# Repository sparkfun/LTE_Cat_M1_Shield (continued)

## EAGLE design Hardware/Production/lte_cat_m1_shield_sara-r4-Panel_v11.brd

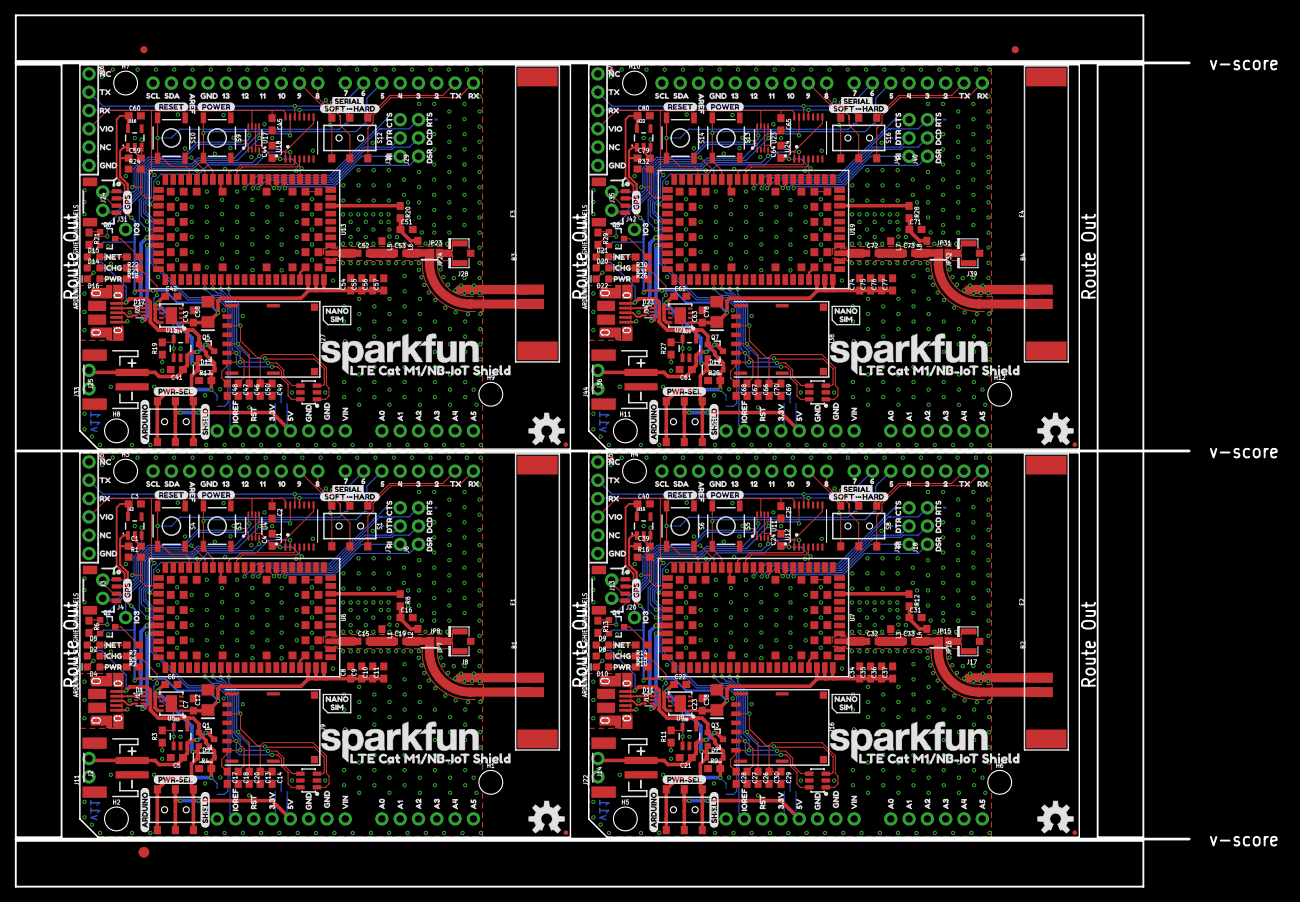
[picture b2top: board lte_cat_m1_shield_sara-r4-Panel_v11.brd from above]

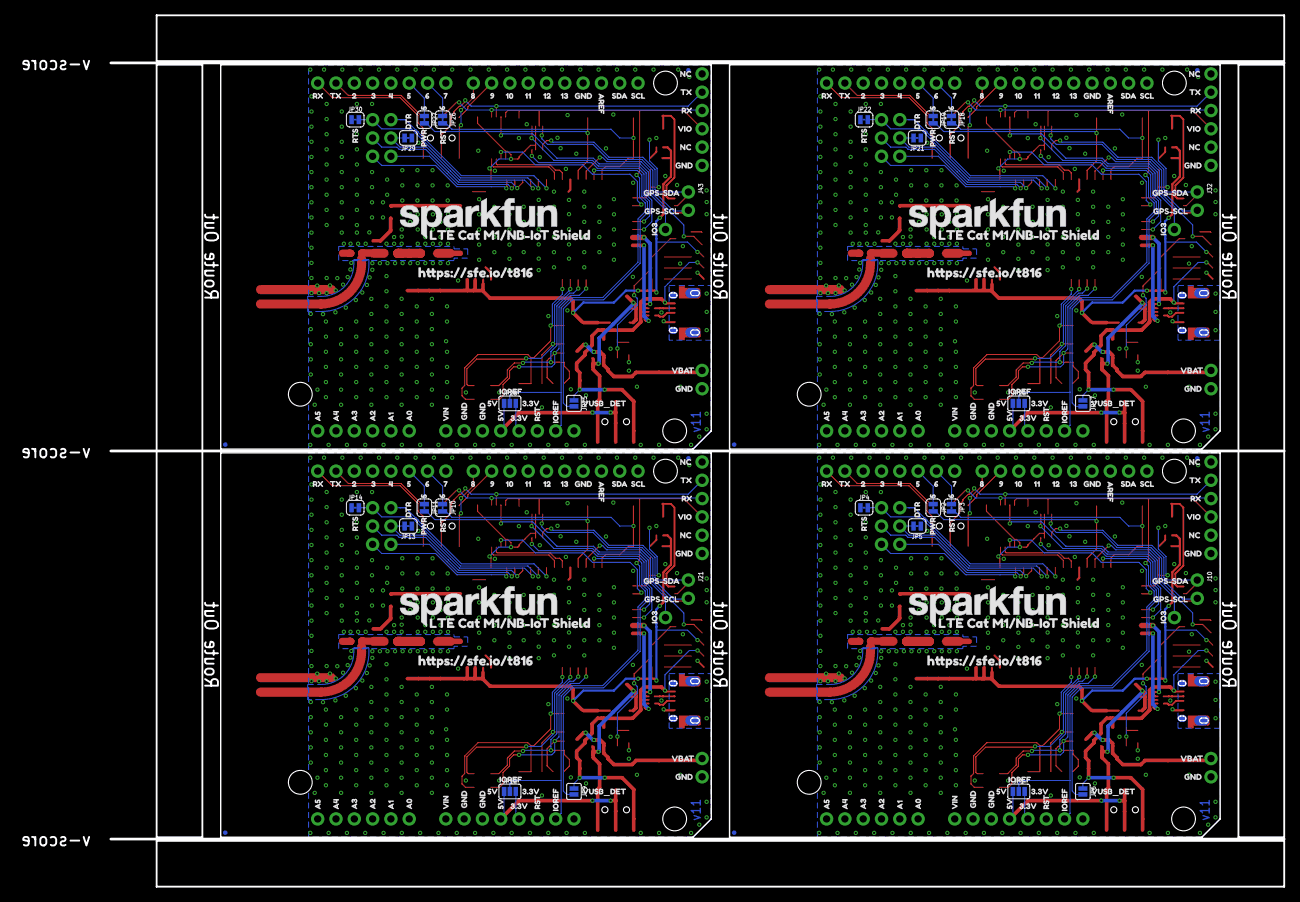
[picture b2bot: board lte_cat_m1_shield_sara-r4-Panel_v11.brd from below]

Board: 2 copper layers, 162.8 x 120.9 mm, 767 parts (256 on the bottom side), 240 nets.

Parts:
B1, B2, B3, B4: ARDUINO_UNO_R3_SHIELDNOLABELS; UNO_R3_SHIELD_NOLABELS
C1, C3, C39, C40, C59, C60, C79, C80: 1.0uF; 0603
C2, C4, C8, C13, C24, C25, C30, C34, C44, C45, C50, C54, C64, C65, C70, C74: 0.1uF; 0603
C5, C6, C7, C21, C22, C23, C41, C42, C43, C61, C62, C63: 4.7uF; 0603
C9, C35, C55, C75: 10nF; 0603
C10, C15, C32, C36, C52, C56, C72, C76: 15pF; 0603
C11, C37, C57, C77: 68pF; 0603
C12, C38, C58, C78: 100uF; 1206-POLAR
C14, C17, C18, C20, C26, C27, C28, C29, C46, C47, C48, C49, C66, C67, C68, C69: 47pF; 0603
C16, C31, C51, C71: DNP; 0603
C19, C33, C53, C73: 0; 0603
D1, D11, D17, D23: PRTR5V0U2F; SOT886
D2, D8, D14, D20: Yellow; LED-0603
D3, D7, D13, D19: 1A/23V/620mV; SOD-323
D4, D10, D16, D22: RED; LED-0603
D5, D9, D15, D21: BLUE; LED-0603
D6, D12, D18, D24: DT1042-04SO-7; SOT23-6L
E1, E2, E3, E4: MOLEX-146200; MOLEX_146200
E$1, E$2: FIDUCIAL-1X2
E$3: FIDUCIAL-1.5X3
FD1, FD2, FD3, FD4, FD5, FD6, FD7, FD8, FD9, FD10, FD11, FD12, FD13, FD14, FD15, FD16: FIDUCIALUFIDUCIAL; FIDUCIAL-MICRO
H1, H2, H3, H4, H5, H6, H7, H8, H9, H10, H11, H12: STAND-OFF
J1, J12, J23, J34: USB-MICROB-PTH-MILL
J2, J14, J25, J36: JST-2-SMD
J3, J13, J24, J35: 1X04_1MM_RA
J4, J20, J31, J42: 1X01_NO_SILK
J5, J15, J26, J37: 1X06_NO_SILK
J6, J7, J18, J19, J29, J30, J40, J41: 1X03_NO_SILK
J8, J17, J28, J39: U.FL
J9, J16, J27, J38: NANO_SIM; NANO_SIM_WURTH_693043020611
J10, J11, J21, J22, J32, J33, J43, J44: 1X02_NO_SILK
JP1, JP12, JP20, JP28: IOREF-SEL; SMT-JUMPER_3_NO_SILK
JP2, JP3, JP10, JP11, JP18, JP19, JP26, JP27: JUMPER-SMT_2_NC_TRACE_SILK; SMT-JUMPER_2_NC_TRACE_SILK
JP4, JP5, JP13, JP14, JP21, JP22, JP29, JP30: SMT-JUMPER_2_NC_TRACE_SILK
JP6, JP9, JP17, JP25: VUSB_DET; SMT-JUMPER_2_NO_SILK
JP7, JP16, JP24, JP32: J-CHIP; SMT-JUMPER_2_NC_TRACE_NO-SILK
JP8, JP15, JP23, JP31: J-U.FL; SMT-JUMPER_2_NO_NO-SILK
L1, L3, L5, L7: 39nH; 0603
L2, L4, L6, L8: DNP; 0603
LOGO1, LOGO3, LOGO5, LOGO6, LOGO8, LOGO9, LOGO11, LOGO12: SFE_LOGO_NAME.2_INCH; SFE_LOGO_NAME_.2
LOGO2, LOGO4, LOGO7, LOGO10: OSHW-LOGOM; OSHW-LOGO-M
Q1, Q3, Q5, Q7: 2.5A/30V/105mΩ; SOT23-3
Q2, Q4, Q6, Q8: 600mA/40V; SOT23-3
R1, R16, R24, R32: 47k; 0603
R2, R5, R7, R10, R14, R15, R18, R22, R23, R26, R30, R31: 1k; 0603
R3, R11, R19, R27: 2.0k; 0603
R4, R6, R9, R13, R17, R21, R25, R29: 10k; 0603
R8, R12, R20, R28: DNP; 0603
S1, S2, S7, S8, S11, S12, S15, S16: SWITCH_DPDT_SMD_AYZ0202
S3, S5, S9, S13: PWR_ON; TACTILE_SWITCH_SMD_5.2MM
S4, S6, S10, S14: RESET; TACTILE_SWITCH_SMD_5.2MM
U1, U12, U18, U24: TXB0104; TSSOP14
U2, U10, U16, U22: AP2112K-3.3; SOT23-5
U3, U8, U14, U20: MCP73831; SOT23-5
U4, U11, U17, U23: TCA9406DCU; VSSOP-8
U5, U9, U15, U21: AP7361C-33FGE; 8-UDFN
U6, U7, U13, U19: SARA-R410M-2B; SARA-LGA
U$1, U$85, U$113, U$185, U$225, U$297, U$337, U$409: SCL0
U$2, U$84, U$114, U$184, U$226, U$296, U$338, U$408: SDA1
U$3, U$86, U$115, U$186, U$227, U$298, U$339, U$410: AREF2
U$4, U$45, U$46, U$73, U$74, U$88, U$104, U$105, U$112, U$116, U$147, U$148, U$175, U$176, U$188, U$202, U$203, U$222, U$228, U$259, U$260, U$287, U$288, U$300, U$314, U$315, U$334, U$340, U$371, U$372, U$399, U$400, U$412, U$426, U$427, U$446: GND3
U$5, U$87, U$117, U$187, U$229, U$299, U$341, U$411: 134
U$6, U$89, U$118, U$189, U$230, U$301, U$342, U$413: 125
U$7, U$90, U$119, U$190, U$231, U$302, U$343, U$414: 116
U$8, U$91, U$120, U$191, U$232, U$303, U$344, U$415: 107
U$9, U$92, U$121, U$192, U$233, U$304, U$345, U$416: 98
U$10, U$93, U$122, U$193, U$234, U$305, U$346, U$417: 89
U$11, U$207, U$319, U$431: RESET48
U$12, U$208, U$320, U$432: GPS47
U$13, U$94, U$123, U$194, U$235, U$306, U$347, U$418: 714
U$14, U$62, U$95, U$124, U$164, U$195, U$236, U$276, U$307, U$348, U$388, U$419: 615
U$15, U$61, U$96, U$125, U$163, U$196, U$237, U$275, U$308, U$349, U$387, U$420: 516
U$16, U$97, U$126, U$197, U$238, U$309, U$350, U$421: 417
U$17, U$98, U$127, U$198, U$239, U$310, U$351, U$422: 318
U$18, U$99, U$128, U$199, U$240, U$311, U$352, U$423: 219
U$19, U$206, U$318, U$430: POWER49
U$20, U$30, U$81, U$101, U$129, U$138, U$182, U$201, U$241, U$250, U$294, U$313, U$353, U$362, U$406, U$425: RX22
U$21, U$31, U$80, U$100, U$130, U$139, U$181, U$200, U$242, U$251, U$293, U$312, U$354, U$363, U$405, U$424: TX21
U$22, U$205, U$317, U$429: SERIAL57
U$23, U$131, U$243, U$355: CTS23
U$24, U$63, U$132, U$165, U$244, U$277, U$356, U$389: DTR24
U$25, U$133, U$245, U$357: RI25
U$26, U$134, U$246, U$358: DSR26
U$27, U$135, U$247, U$359: DCD27
U$28, U$64, U$136, U$166, U$248, U$278, U$360, U$390: RTS28
U$29, U$82, U$137, U$183, U$249, U$295, U$361, U$407: VIO29
U$32, U$77, U$223, U$224, U$335, U$336, U$447, U$448: LTE_CAT_M1#NB#IOT_SHIELD1
U$33, U$209, U$321, U$433: ARDUINO51
U$34, U$79, U$140, U$180, U$252, U$292, U$364, U$404: IO334
U$35, U$141, U$253, U$365: NET31
U$36, U$142, U$254, U$366: CHG33
U$37, U$59, U$143, U$161, U$255, U$273, U$367, U$385: PWR32
U$38, U$211, U$323, U$435: PWR#SEL53
U$39, U$210, U$322, U$434: SHIELD52
U$40, U$42, U$212, U$213, U$324, U$325, U$436, U$437: RST0
U$41, U$56, U$78, U$144, U$158, U$179, U$256, U$270, U$291, U$368, U$382, U$403: IOREF39
U$43, U$58, U$76, U$145, U$160, U$178, U$257, U$272, U$290, U$369, U$384, U$402: 3#3V41
U$44, U$57, U$75, U$146, U$159, U$177, U$258, U$271, U$289, U$370, U$383, U$401: 5V42
U$47, U$72, U$149, U$174, U$261, U$286, U$373, U$398: VIN43
U$48, U$71, U$150, U$173, U$262, U$285, U$374, U$397: A044
U$49, U$70, U$151, U$172, U$263, U$284, U$375, U$396: A145
U$50, U$69, U$152, U$171, U$264, U$283, U$376, U$395: A246
U$51, U$68, U$153, U$170, U$265, U$282, U$377, U$394: A347
U$52, U$67, U$154, U$169, U$266, U$281, U$378, U$393: A448
U$53, U$66, U$155, U$168, U$267, U$280, U$379, U$392: A549
U$54, U$156, U$268, U$380: NANO50
U$55, U$157, U$269, U$381: SIM51
U$60, U$162, U$274, U$386: RST40
U$65, U$167, U$279, U$391: VUSB_DET52
U$83, U$214, U$326, U$438: HTTPS###SFE#IO#T8160
U$102, U$204, U$316, U$428: SOFT#HARD50
U$103, U$106, U$107, U$108, U$215, U$216, U$217, U$218, U$327, U$328, U$329, U$330, U$439, U$440, U$441, U$442: NC0
U$109, U$219, U$331, U$443: GPS#SCL1
U$110, U$220, U$332, U$444: GPS#SDA0
U$111, U$221, U$333, U$445: VBAT2

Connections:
1.8V: C4.1, U1.1, U1.8, U4.3, U4.6, U6.4
1.8V1: C24.1, U7.4, U11.3, U11.6, U12.1, U12.8
1.8V2: C44.1, U13.4, U17.3, U17.6, U18.1, U18.8
1.8V3: C64.1, U19.4, U23.3, U23.6, U24.1, U24.8
3.3V: C1.1, C7.1, C8.1, C9.1, C10.1, C11.1, C12.1, D5.A, R5.2, U2.1, U5.1, U6.51, U6.52, U6.53
3.3V1: C23.1, C34.1, C35.1, C36.1, C37.1, C38.1, C39.1, D9.A, R15.2, U7.51, U7.52, U7.53, U9.1, U10.1
3.3V2: C43.1, C54.1, C55.1, C56.1, C57.1, C58.1, C59.1, D15.A, R23.2, U13.51, U13.52, U13.53, U15.1, U16.1
3.3V3: C63.1, C74.1, C75.1, C76.1, C77.1, C78.1, C79.1, D21.A, R31.2, U19.51, U19.52, U19.53, U21.1, U22.1
ANT: C15.1, U6.56
ANT1: C32.1, U7.56
ANT2: C52.1, U13.56
ANT3: C72.1, U19.56
ANT_DET: R8.1, U6.62
ANT_DET1: R12.1, U7.62
ANT_DET2: R20.1, U13.62
ANT_DET3: R28.1, U19.62
ARDUINO-3.3V: B1.3.3V, JP1.3
ARDUINO-3.3V1: B2.3.3V, JP12.3
ARDUINO-3.3V2: B3.3.3V, JP20.3
ARDUINO-3.3V3: B4.3.3V, JP28.3
ARDUINO-5V: B1.5V, JP1.1, S2.2, S2.5
ARDUINO-5V1: B2.5V, JP12.1, S7.2, S7.5
ARDUINO-5V2: B3.5V, JP20.1, S11.2, S11.5
ARDUINO-5V3: B4.5V, JP28.1, S15.2, S15.5
CTS: J7.3, U6.11
CTS1: J19.3, U7.11
CTS2: J30.3, U13.11
CTS3: J41.3, U19.11
D+: D1.4, U6.29
D+1: D11.4, U7.29
D+2: D17.4, U13.29
D+3: D23.4, U19.29
D-: D1.6, U6.28
D-1: D11.6, U7.28
D-2: D17.6, U13.28
D-3: D23.6, U19.28
DCD: J6.2, U6.8
DCD1: J18.2, U7.8
DCD2: J29.2, U13.8
DCD3: J40.2, U19.8
DSR: J6.1, U6.6
DSR1: J18.1, U7.6
DSR2: J29.1, U13.6
DSR3: J40.1, U19.6
DTR: J7.2, JP5.2, U6.9
DTR1: J19.2, JP13.2, U7.9
DTR2: J30.2, JP21.2, U13.9
DTR3: J41.2, JP29.2, U19.9
GND: B1.GND@0, B1.GND@1, B1.GND@2, C1.2, C2.2, C3.2, C4.2, C5.2, C6.2, C7.2, C8.2, C9.2, C10.2, C11.2, C12.2, C13.2, C14.2, C16.2, C17.2, C18.2, C20.2, D1.2, D4.C, D6.2, D6.5, E1.GND, J1.GND, J2.1, J3.1, J5.6, J8.1, J8.2, J9.C5, J11.1, JP4.1, JP5.1, L1.1, Q2.2, R1.1, R3.1, R4.1, S3.1, S3.2, S4.1, S4.2, U1.7, U2.2, U3.2, U4.2, U5.4, U5.EP, U6.1, U6.3, U6.5, U6.14, U6.20, U6.21, U6.22, U6.30, U6.32, U6.33, U6.43, U6.50, U6.54, U6.55, U6.57, U6.58, U6.59, U6.60, U6.61, U6.63, U6.64, U6.65, U6.66, U6.67, U6.68, U6.69, U6.70, U6.71, U6.72, U6.73, U6.74, U6.75, U6.76, U6.77, U6.78, U6.79, U6.80, U6.81, U6.82, U6.83, U6.84, U6.85, U6.86, U6.87, U6.88, U6.89, U6.90, U6.91, U6.92, U6.93, U6.94, U6.95, U6.96
GND1: B2.GND@0, B2.GND@1, B2.GND@2, C21.2, C22.2, C23.2, C24.2, C25.2, C26.2, C27.2, C28.2, C29.2, C30.2, C31.2, C34.2, C35.2, C36.2, C37.2, C38.2, C39.2, C40.2, D10.C, D11.2, D12.2, D12.5, E2.GND, J12.GND, J13.1, J14.1, J15.6, J16.C5, J17.1, J17.2, J22.1, JP13.1, JP14.1, L3.1, Q4.2, R9.1, R11.1, R16.1, S5.1, S5.2, S6.1, S6.2, U7.1, U7.3, U7.5, U7.14, U7.20, U7.21, U7.22, U7.30, U7.32, U7.33, U7.43, U7.50, U7.54, U7.55, U7.57, U7.58, U7.59, U7.60, U7.61, U7.63, U7.64, U7.65, U7.66, U7.67, U7.68, U7.69, U7.70, U7.71, U7.72, U7.73, U7.74, U7.75, U7.76, U7.77, U7.78, U7.79, U7.80, U7.81, U7.82, U7.83, U7.84, U7.85, U7.86, U7.87, U7.88, U7.89, U7.90, U7.91, U7.92, U7.93, U7.94, U7.95, U7.96, U8.2, U9.4, U9.EP, U10.2, U11.2, U12.7
GND2: B3.GND@0, B3.GND@1, B3.GND@2, C41.2, C42.2, C43.2, C44.2, C45.2, C46.2, C47.2, C48.2, C49.2, C50.2, C51.2, C54.2, C55.2, C56.2, C57.2, C58.2, C59.2, C60.2, D16.C, D17.2, D18.2, D18.5, E3.GND, J23.GND, J24.1, J25.1, J26.6, J27.C5, J28.1, J28.2, J33.1, JP21.1, JP22.1, L5.1, Q6.2, R17.1, R19.1, R24.1, S9.1, S9.2, S10.1, S10.2, U13.1, U13.3, U13.5, U13.14, U13.20, U13.21, U13.22, U13.30, U13.32, U13.33, U13.43, U13.50, U13.54, U13.55, U13.57, U13.58, U13.59, U13.60, U13.61, U13.63, U13.64, U13.65, U13.66, U13.67, U13.68, U13.69, U13.70, U13.71, U13.72, U13.73, U13.74, U13.75, U13.76, U13.77, U13.78, U13.79, U13.80, U13.81, U13.82, U13.83, U13.84, U13.85, U13.86, U13.87, U13.88, U13.89, U13.90, U13.91, U13.92, U13.93, U13.94, U13.95, U13.96, U14.2, U15.4, U15.EP, U16.2, U17.2, U18.7
GND3: B4.GND@0, B4.GND@1, B4.GND@2, C61.2, C62.2, C63.2, C64.2, C65.2, C66.2, C67.2, C68.2, C69.2, C70.2, C71.2, C74.2, C75.2, C76.2, C77.2, C78.2, C79.2, C80.2, D22.C, D23.2, D24.2, D24.5, E4.GND, J34.GND, J35.1, J36.1, J37.6, J38.C5, J39.1, J39.2, J44.1, JP29.1, JP30.1, L7.1, Q8.2, R25.1, R27.1, R32.1, S13.1, S13.2, S14.1, S14.2, U19.1, U19.3, U19.5, U19.14, U19.20, U19.21, U19.22, U19.30, U19.32, U19.33, U19.43, U19.50, U19.54, U19.55, U19.57, U19.58, U19.59, U19.60, U19.61, U19.63, U19.64, U19.65, U19.66, U19.67, U19.68, U19.69, U19.70, U19.71, U19.72, U19.73, U19.74, U19.75, U19.76, U19.77, U19.78, U19.79, U19.80, U19.81, U19.82, U19.83, U19.84, U19.85, U19.86, U19.87, U19.88, U19.89, U19.90, U19.91, U19.92, U19.93, U19.94, U19.95, U19.96, U20.2, U21.4, U21.EP, U22.2, U23.2, U24.7
GPIO1: R6.2, U6.16
GPIO2: R1.2, U2.3, U6.23
GPIO3: R13.2, U7.16
GPIO3-CELL: U1.2, U6.24
GPIO3-CELL1: U7.24, U12.2
GPIO3-CELL2: U13.24, U18.2
GPIO3-CELL3: U19.24, U24.2
GPIO3-QWIIC: J4.1, U1.13
GPIO3-QWIIC1: J20.1, U12.13
GPIO3-QWIIC2: J31.1, U18.13
GPIO3-QWIIC3: J42.1, U24.13
GPIO4: R16.2, U7.23, U10.3
GPIO5: R21.2, U13.16
GPIO6: R24.2, U13.23, U16.3
GPIO7: R29.2, U19.16
GPIO8: R32.2, U19.23, U22.3
GPS-3.3V: C3.1, J3.2, U2.5
GPS-3.3V1: C40.1, J13.2, U10.5
GPS-3.3V2: C60.1, J24.2, U16.5
GPS-3.3V3: C80.1, J35.2, U22.5
HARDRX-ARDUINO: B1.RX, S1.1
HARDRX-ARDUINO1: B2.RX, S8.1
HARDRX-ARDUINO2: B3.RX, S12.1
HARDRX-ARDUINO3: B4.RX, S16.1
HARDTX-ARDUINO: B1.TX, S1.4
HARDTX-ARDUINO1: B2.TX, S8.4
HARDTX-ARDUINO2: B3.TX, S12.4
HARDTX-ARDUINO3: B4.TX, S16.4
IOREF: B1.IOREF, C2.1, J5.4, JP1.2, U1.14, U4.7
IOREF1: B2.IOREF, C25.1, J15.4, JP12.2, U11.7, U12.14
IOREF2: B3.IOREF, C45.1, J26.4, JP20.2, U17.7, U18.14
IOREF3: B4.IOREF, C65.1, J37.4, JP28.2, U23.7, U24.14
unnamed: R3.2, U3.5
unnamed: D8.C, R10.2
unnamed: R10.1, U8.1
unnamed: R11.2, U8.5
unnamed: C31.1, L4.2, R12.2
unnamed: C32.2, C33.1, L3.2
unnamed: C16.1, L2.2, R8.2
unnamed: C15.2, C19.1, L1.2
unnamed: J8.FEED, JP8.2
unnamed: Q2.1, R6.1
unnamed: D1.1, J1.D-
unnamed: D5.C, R7.2
unnamed: D1.3, J1.D+
unnamed: Q2.3, R7.1
unnamed: D4.A, R5.1
unnamed: D2.C, R2.2
unnamed: R2.1, U3.1
unnamed: B1.D5, JP2.1
unnamed: B1.D6, JP3.1
unnamed: C19.2, JP7.1, JP8.1, L2.1
unnamed: E1.FEED, JP7.2
unnamed: J17.FEED, JP15.2
unnamed: Q4.1, R13.1
unnamed: D10.A, R15.1
unnamed: D9.C, R14.2
unnamed: Q4.3, R14.1
unnamed: B2.D5, JP11.1
unnamed: B2.D6, JP10.1
unnamed: C33.2, JP15.1, JP16.1, L4.1
unnamed: E2.FEED, JP16.2
unnamed: D11.1, J12.D-
unnamed: D11.3, J12.D+
unnamed: D14.C, R18.2
unnamed: R18.1, U14.1
unnamed: R19.2, U14.5
unnamed: C51.1, L6.2, R20.2
unnamed: C52.2, C53.1, L5.2
unnamed: J28.FEED, JP23.2
unnamed: Q6.1, R21.1
unnamed: D16.A, R23.1
unnamed: D15.C, R22.2
unnamed: Q6.3, R22.1
unnamed: B3.D5, JP19.1
unnamed: B3.D6, JP18.1
unnamed: C53.2, JP23.1, JP24.1, L6.1
unnamed: E3.FEED, JP24.2
unnamed: D17.1, J23.D-
unnamed: D17.3, J23.D+
unnamed: D20.C, R26.2
unnamed: R26.1, U20.1
unnamed: R27.2, U20.5
unnamed: C71.1, L8.2, R28.2
unnamed: C72.2, C73.1, L7.2
unnamed: J39.FEED, JP31.2
unnamed: Q8.1, R29.1
unnamed: D22.A, R31.1
unnamed: D21.C, R30.2
unnamed: Q8.3, R30.1
unnamed: B4.D5, JP27.1
unnamed: B4.D6, JP26.1
unnamed: C73.2, JP31.1, JP32.1, L8.1
unnamed: E4.FEED, JP32.2
unnamed: D23.1, J34.D-
unnamed: D23.3, J34.D+
PWR_ON: JP2.2, S3.3, S3.4, U6.15
PWR_ON1: JP11.2, S5.3, S5.4, U7.15
PWR_ON2: JP19.2, S9.3, S9.4, U13.15
PWR_ON3: JP27.2, S13.3, S13.4, U19.15
RESET_N: JP3.2, S4.3, S4.4, U6.18
RESET_N1: JP10.2, S6.3, S6.4, U7.18
RESET_N2: JP18.2, S10.3, S10.4, U13.18
RESET_N3: JP26.2, S14.3, S14.4, U19.18
RI: J7.1, U6.7
RI1: J19.1, U7.7
RI2: J30.1, U13.7
RI3: J41.1, U19.7
RTS: J6.3, JP4.2, U6.10
RTS1: J18.3, JP14.2, U7.10
RTS2: J29.3, JP22.2, U13.10
RTS3: J40.3, JP30.2, U19.10
RX-ARDUINO: J5.2, S1.2, U1.12
RX-ARDUINO1: J15.2, S8.2, U12.12
RX-ARDUINO2: J26.2, S12.2, U18.12
RX-ARDUINO3: J37.2, S16.2, U24.12
RX-CELL: U1.4, U6.12
RX-CELL1: U7.12, U12.4
RX-CELL2: U13.12, U18.4
RX-CELL3: U19.12, U24.4
SCL-CELL: U4.5, U6.27
SCL-CELL1: U7.27, U11.5
SCL-CELL2: U13.27, U17.5
SCL-CELL3: U19.27, U23.5
SCL-QWIIC: J3.4, J10.2, U4.8
SCL-QWIIC1: J13.4, J21.2, U11.8
SCL-QWIIC2: J24.4, J32.2, U17.8
SCL-QWIIC3: J35.4, J43.2, U23.8
SDA-CELL: U4.4, U6.26
SDA-CELL1: U7.26, U11.4
SDA-CELL2: U13.26, U17.4
SDA-CELL3: U19.26, U23.4
SDA-QWIIC: J3.3, J10.1, U4.1
SDA-QWIIC1: J13.3, J21.1, U11.1
SDA-QWIIC2: J24.3, J32.1, U17.1
SDA-QWIIC3: J35.3, J43.1, U23.1
SHIELD: J1.SHIELD, J1.SHIELD2, J1.SHIELD3, J1.SHIELD4, J1.SHIELD5, J1.SHIELD6, J1.SHIELD7, J1.SHIELD8, J1.SHIELD9, J1.SHIELD10
SHIELD1: J12.SHIELD, J12.SHIELD2, J12.SHIELD3, J12.SHIELD4, J12.SHIELD5, J12.SHIELD6, J12.SHIELD7, J12.SHIELD8, J12.SHIELD9, J12.SHIELD10
SHIELD2: J23.SHIELD, J23.SHIELD2, J23.SHIELD3, J23.SHIELD4, J23.SHIELD5, J23.SHIELD6, J23.SHIELD7, J23.SHIELD8, J23.SHIELD9, J23.SHIELD10
SHIELD3: J34.SHIELD, J34.SHIELD2, J34.SHIELD3, J34.SHIELD4, J34.SHIELD5, J34.SHIELD6, J34.SHIELD7, J34.SHIELD8, J34.SHIELD9, J34.SHIELD10
SIM_CLK: C18.1, D6.6, J9.C3, U6.38
SIM_CLK1: C27.1, D12.6, J16.C3, U7.38
SIM_CLK2: C47.1, D18.6, J27.C3, U13.38
SIM_CLK3: C67.1, D24.6, J38.C3, U19.38
SIM_IO: C17.1, D6.4, J9.C7, U6.39
SIM_IO1: C28.1, D12.4, J16.C7, U7.39
SIM_IO2: C48.1, D18.4, J27.C7, U13.39
SIM_IO3: C68.1, D24.4, J38.C7, U19.39
SIM_RST: C20.1, D6.3, J9.C2, U6.40
SIM_RST1: C26.1, D12.3, J16.C2, U7.40
SIM_RST2: C46.1, D18.3, J27.C2, U13.40
SIM_RST3: C66.1, D24.3, J38.C2, U19.40
SOFTRX-ARDUINO: B1.D8, S1.3
SOFTRX-ARDUINO1: B2.D8, S8.3
SOFTRX-ARDUINO2: B3.D8, S12.3
SOFTRX-ARDUINO3: B4.D8, S16.3
SOFTTX-ARDUINO: B1.D9, S1.6
SOFTTX-ARDUINO1: B2.D9, S8.6
SOFTTX-ARDUINO2: B3.D9, S12.6
SOFTTX-ARDUINO3: B4.D9, S16.6
TX-ARDUINO: J5.3, S1.5, U1.11
TX-ARDUINO1: J15.3, S8.5, U12.11
TX-ARDUINO2: J26.3, S12.5, U18.11
TX-ARDUINO3: J37.3, S16.5, U24.11
TX-CELL: U1.3, U6.13
TX-CELL1: U7.13, U12.3
TX-CELL2: U13.13, U18.3
TX-CELL3: U19.13, U24.3
VIN: C6.1, D3.C, Q1.2, S2.1, S2.4, U5.5, U5.8
VIN1: C22.1, D7.C, Q3.2, S7.1, S7.4, U9.5, U9.8
VIN2: C42.1, D13.C, Q5.2, S11.1, S11.4, U15.5, U15.8
VIN3: C62.1, D19.C, Q7.2, S15.1, S15.4, U21.5, U21.8
VSIM: C13.1, C14.1, D6.1, J9.C1, U6.41
VSIM1: C29.1, C30.1, D12.1, J16.C1, U7.41
VSIM2: C49.1, C50.1, D18.1, J27.C1, U13.41
VSIM3: C69.1, C70.1, D24.1, J38.C1, U19.41
VUSB_DET: JP6.2, U6.17
VUSB_DET1: JP9.2, U7.17
VUSB_DET2: JP17.2, U13.17
VUSB_DET3: JP25.2, U19.17
V_BATT: C5.1, J2.2, J11.2, Q1.3, U3.3
V_BATT1: C21.1, J14.2, J22.2, Q3.3, U8.3
V_BATT2: C41.1, J25.2, J33.2, Q5.3, U14.3
V_BATT3: C61.1, J36.2, J44.2, Q7.3, U20.3
V_USB: D1.5, D2.A, D3.A, J1.VBUS, JP6.1, Q1.1, R4.2, S2.3, S2.6, U3.4
V_USB1: D7.A, D8.A, D11.5, J12.VBUS, JP9.1, Q3.1, R9.2, S7.3, S7.6, U8.4
V_USB2: D13.A, D14.A, D17.5, J23.VBUS, JP17.1, Q5.1, R17.2, S11.3, S11.6, U14.4
V_USB3: D19.A, D20.A, D23.5, J34.VBUS, JP25.1, Q7.1, R25.2, S15.3, S15.6, U20.4

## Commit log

2018-08-15 Initial commit of hardware.
2018-08-15 Minor revisions post-review
2018-08-15 Adding documentation.
2018-08-22 hardware revisions post u-blox review - x02 production hardware
2018-09-13 v10 of the LTE Shield hardware.
2018-09-14 Removing single-board gerber files.
2018-09-14 DNP'ing the antenna-detect circuit.
2018-09-14 Revisions post-checklist.
2018-09-14 Adding production IDs to new parts.
2018-09-14 Modification post-group-review. Labels, Qwiic breakouts, test points.
2018-09-18 Revising product name in silk, schematic fixes.
2018-09-18 panel v10 created
2019-12-09 Disconnected AREF from GND
2019-12-13 Production panel v11
    Also updated sch pdf
2023-04-27 Update README.md
    Update product image link
2023-04-27 Update README.md
    Add version history
